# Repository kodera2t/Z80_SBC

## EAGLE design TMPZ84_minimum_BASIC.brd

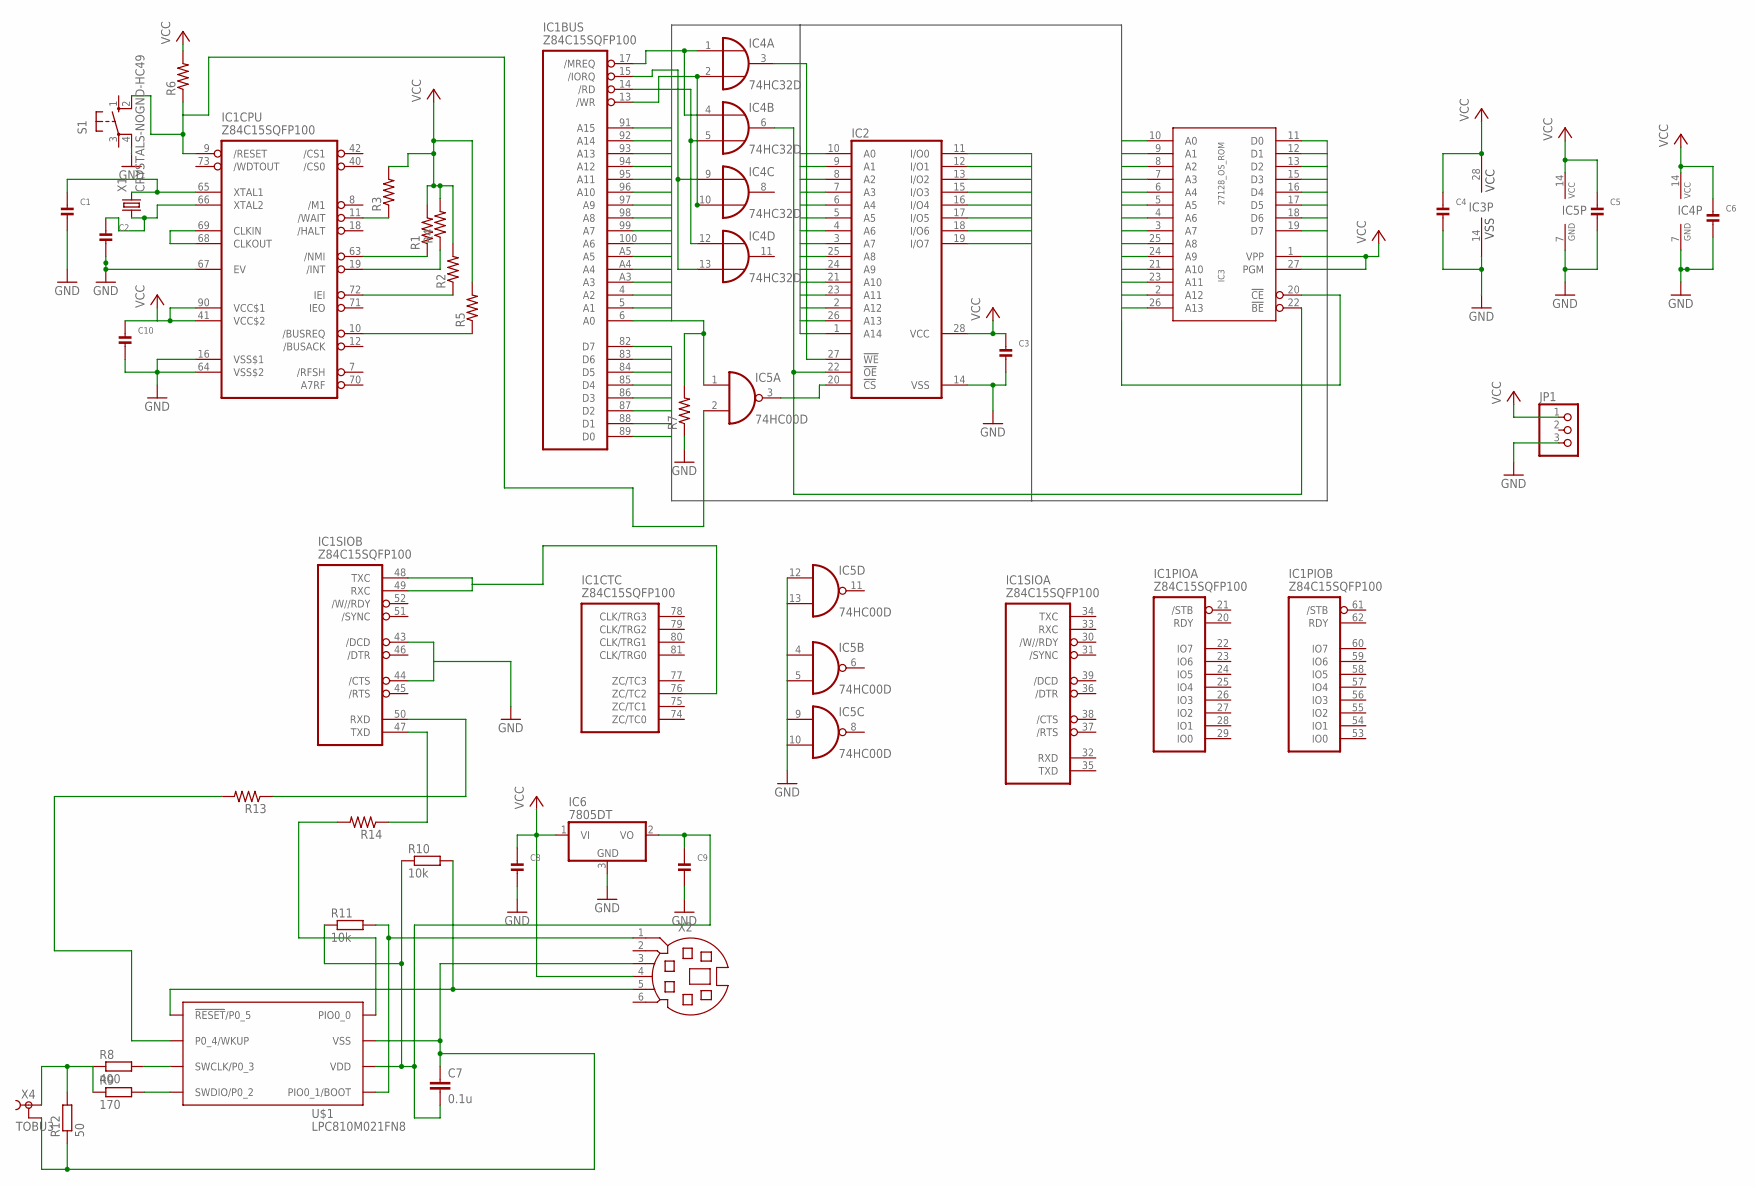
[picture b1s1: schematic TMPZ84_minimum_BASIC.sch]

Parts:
C1, C2, C3, C4, C5, C6, C8, C9, C10: CAP_CERAMIC0603; 0603
C7: 0.1u; C0603
IC1: Z84C15SQFP100; SQFP-R-14X20-100
IC2: 62256FP; SO28L
IC3: 27128_OS_ROM; DIL28
IC4: 74HC32D; SO14
IC5: 74HC00D; SO14
IC6: 7805DT; TO252
JP1: PINHD-1X3; 1X03
R1, R2, R3, R4, R5, R6, R7, R13, R14: R-US_R0603; R0603
R8: 400; R0603
R9: 170; R0603
R10, R11: 10k; R0603
R12: 50; R0603
S1: 10-XX; B3F-10XX
U$1: LPC810M021FN8; DIP8
X1: CRYSTALS-NOGND-HC49; HC49
X2: MD06S; MDIN06S
X4: TOBU3

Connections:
A0: IC1.6 (A0), IC2.10 (A0), IC3.10 (A0)
A1: IC1.5 (A1), IC2.9 (A1), IC3.9 (A1)
A2: IC1.4 (A2), IC2.8 (A2), IC3.8 (A2)
A3: IC1.A3, IC2.7 (A3), IC3.7 (A3)
A4: IC1.A4, IC2.6 (A4), IC3.6 (A4)
A5: IC1.A5, IC2.5 (A5), IC3.5 (A5)
A6: IC1.100 (A6), IC2.4 (A6), IC3.4 (A6)
A7: IC1.99 (A7), IC2.3 (A7), IC3.3 (A7)
A8: IC1.98 (A8), IC2.25 (A8), IC3.25 (A8)
A9: IC1.97 (A9), IC2.24 (A9), IC3.24 (A9)
A10: IC1.96 (A10), IC2.21 (A10), IC3.21 (A10)
A11: IC1.95 (A11), IC2.23 (A11), IC3.23 (A11)
A12: IC1.93 (A13), IC1.94 (A12), IC2.2 (A12), IC3.2 (A12)
A13: IC2.26 (A13), IC3.26 (A13)
A14: IC1.92 (A14), IC2.1 (A14)
A15: IC1.91 (A15), IC3.20 (!CE), IC5.1 (I0), R7.2
D0: IC1.89 (D0), IC2.11 (I/O0), IC3.11 (D0)
D1: IC1.88 (D1), IC2.12 (I/O1), IC3.12 (D1)
D2: IC1.87 (D2), IC2.13 (I/O2), IC3.13 (D2)
D3: IC1.86 (D3), IC2.15 (I/O3), IC3.15 (D3)
D4: IC1.85 (D4), IC2.16 (I/O4), IC3.16 (D4)
D5: IC1.84 (D5), IC2.17 (I/O5), IC3.17 (D5)
D6: IC1.83 (D6), IC2.18 (I/O6), IC3.18 (D6)
D7: IC1.82 (D7), IC2.19 (I/O7), IC3.19 (D7)
GND: C1.2, C2.2, C3.2, C4.2, C5.2, C6.2, C8.2, C9.2, C10.2, IC1.16 (VSS$1), IC1.43 (/DCD), IC1.44 (/CTS), IC1.64 (VSS$2), IC1.67 (EV), IC2.14 (VSS), IC3.14 (VSS), IC4.7 (GND), IC5.4 (I0), IC5.5 (I1), IC5.7 (GND), IC5.9 (I0), IC5.10 (I1), IC5.12 (I0), IC5.13 (I1), IC6.3 (GND), JP1.3, R7.1, S1.4 (P1)
unnamed: C1.1, IC1.65 (XTAL1), X1.2
unnamed: C2.1, IC1.66 (XTAL2), X1.1
unnamed: IC1.17 (/MREQ), IC4.1 (I0), IC4.4 (I0)
unnamed: C7.2, C9.1, IC6.2 (VO), R10.1, R11.1, U$1.P$6 (VDD)
unnamed: IC1.13 (/WR), IC4.2 (I1), IC4.10 (I1)
unnamed: IC1.14 (/RD), IC4.5 (I1), IC4.12 (I0)
unnamed: IC1.15 (/IORQ), IC4.9 (I0), IC4.13 (I1)
unnamed: IC2.22 (!OE), IC3.22 (!BE), IC4.6 (O)
unnamed: IC2.27 (!WE), IC4.3 (O)
unnamed: IC1.68 (CLKOUT), IC1.69 (CLKIN)
unnamed: IC1.72 (IEI), R2.1
unnamed: IC1.63 (/NMI), R1.1
unnamed: IC2.20 (!CS), IC5.3 (O)
unnamed: IC1.50 (RXD), R13.1
unnamed: IC1.19 (/INT), R4.1
unnamed: IC1.11 (/WAIT), R3.1
unnamed: IC1.48 (TXC), IC1.49 (RXC), IC1.76 (ZC/TC2)
unnamed: IC1.10 (/BUSREQ), R5.1
unnamed: R11.2, U$1.P$5 (PIO0_1/BOOT), X2.1
unnamed: IC1.9 (/RESET), IC5.2 (I1), R6.1, S1.2 (S1)
unnamed: IC1.47 (TXD), R14.1
unnamed: R10.2, U$1.P$1 (!RESET!/P0_5), X2.5
unnamed: R8.2, U$1.P$3 (SWCLK/P0_3)
unnamed: R9.2, U$1.P$4 (SWDIO/P0_2)
unnamed: R8.1, R9.1, R12.2, X4.1
unnamed: C7.1, R12.1, U$1.P$7 (VSS), X2.3, X4.2, X4.2@1 (2), X4.2@2 (2)
unnamed: R13.2, U$1.P$2 (P0_4/WKUP)
unnamed: R14.2, U$1.P$8 (PIO0_0)
VCC: C3.1, C4.1, C5.1, C6.1, C8.1, C10.1, IC1.41 (VCC$2), IC1.90 (VCC$1), IC2.28 (VCC), IC3.1 (VPP), IC3.27 (PGM), IC3.28 (VCC), IC4.14 (VCC), IC5.14 (VCC), IC6.1 (VI), JP1.1, R1.2, R2.2, R3.2, R4.2, R5.2, R6.2, X2.4

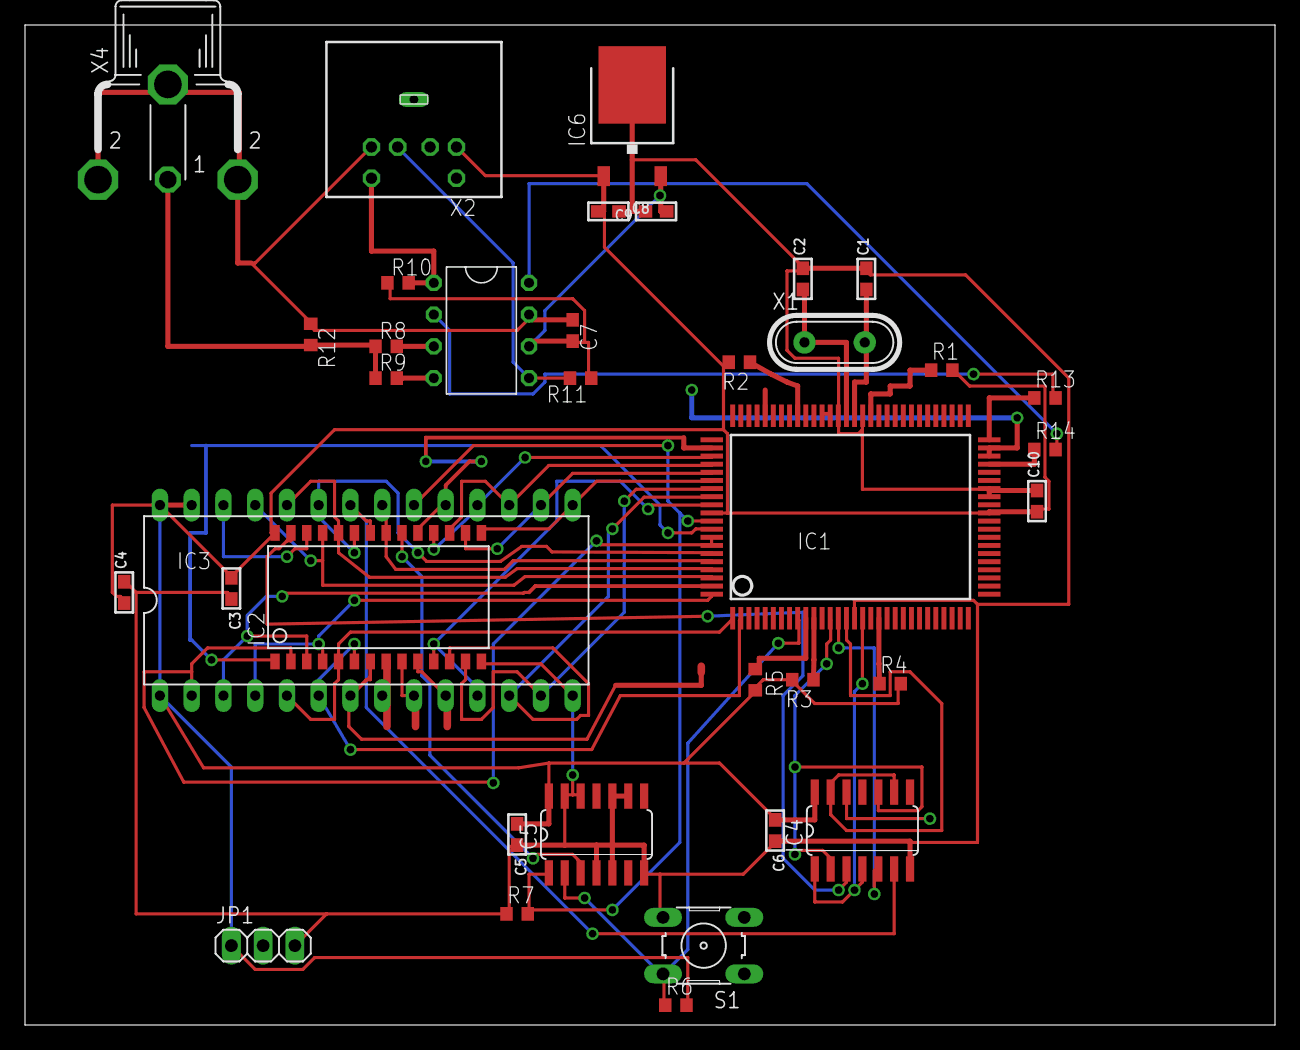
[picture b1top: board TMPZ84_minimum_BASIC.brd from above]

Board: 2 copper layers, 100.0 x 80.0 mm, 36 parts (0 on the bottom side), 54 nets.

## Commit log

2015-12-29 TMPZ84C015
    Initial submission. Please find lots of jumper (yellow lines) by eagle,
    and not forget to connect them…

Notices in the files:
parts and their libraries:
OLED_mod: This work is placed in the public domain, and may be freely used for commercial and non-commercial work with the following conditions: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
eagle-6.5.0-atari: Copyright (c) 2010
Copyright (c) 2009
This library is licensed under the
Creative Commons Attribution 3.0 United States License.
